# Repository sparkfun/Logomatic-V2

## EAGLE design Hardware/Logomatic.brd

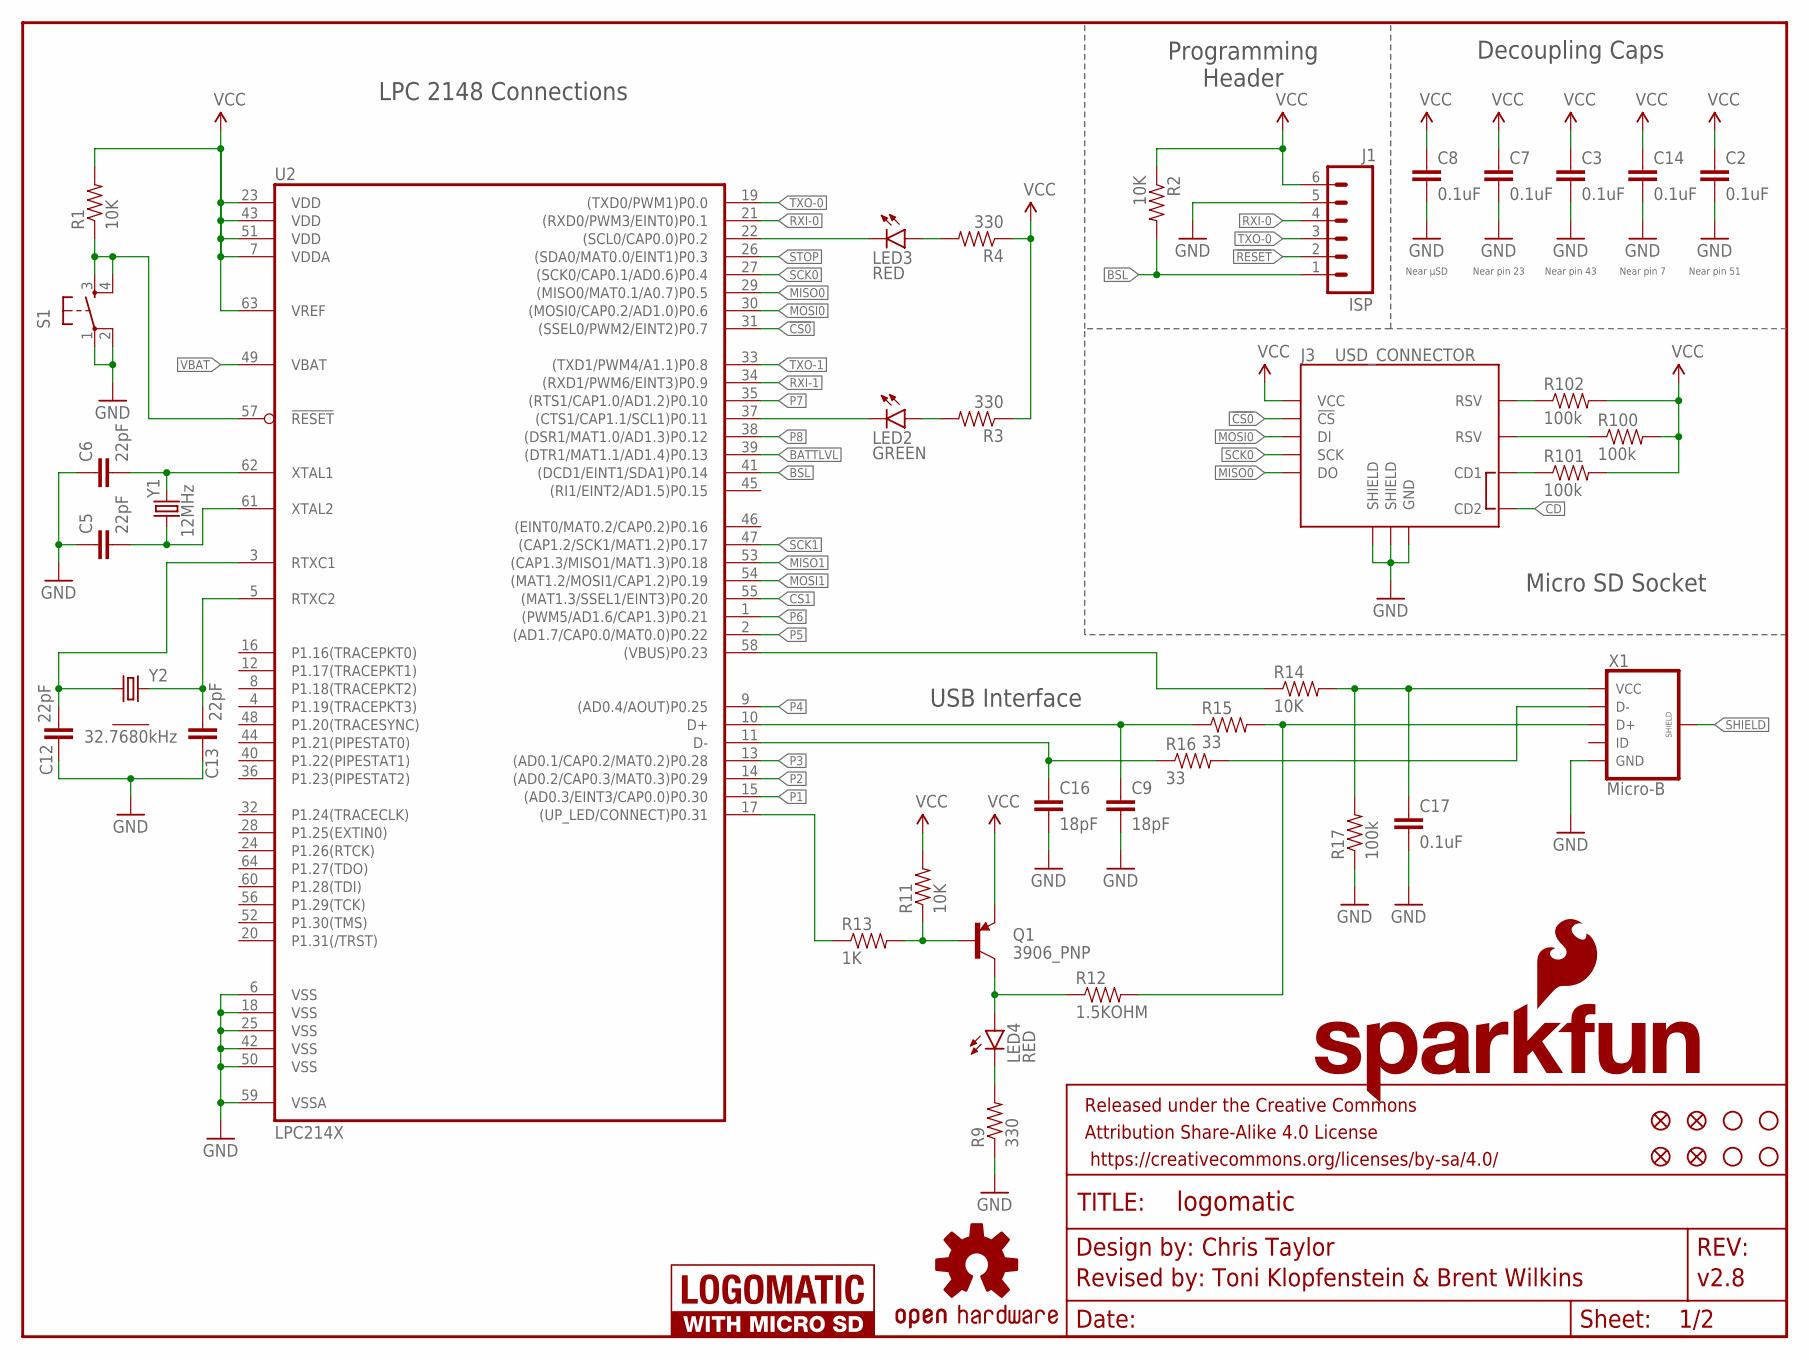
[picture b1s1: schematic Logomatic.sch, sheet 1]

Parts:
C2, C3, C7, C8, C14, C17: 0.1uF; 0603-CAP
C5, C6, C12, C13: 22pF; 0603-CAP
C9, C16: 18pF; 0603-CAP
FD1, FD2, FD100, FD101: FIDUCIAL1X2; FIDUCIAL-1X2
FRAME1: FRAME-LETTER; CREATIVE_COMMONS
H1, H2, H3, H4: STAND-OFF
J1: ISP; 1X06
J3: USD_CONNECTOR; MICRO-SD-SOCKET-PP
LED2: GREEN; LED-0603
LED3, LED4: RED; LED-0603
LOGO1: SFE_LOGO_NAME.1_INCH; SFE_LOGO_NAME_.1
LOGO2: SFE_LOGO_FLAME.1_INCH; SFE_LOGO_FLAME_.1
LOGO100: OSHW-LOGOL; OSHW-LOGO-L
LOGO101: LOGOMATIC_LOGO
Q1: 3906_PNP; SOT23-3
R1, R2, R11, R14: 10K; 0603-RES
R3, R4, R9: 330; 0603-RES
R12: 1.5KOHM; 0603
R13: 1K; 0603-RES
R15, R16: 33; 0603-RES
R17, R100, R101, R102: 100k; 0603-RES
S1: RESET; TACTILE-SWITCH-SMD
U2: LPC214X; LQFP-10X10-64
X1: Micro-B; USB-B-MICRO-SMD_V03
Y1: 12MHz; CRYSTAL-SMD-5X3
Y2: 32.7680kHz; 4-SOJ_5.5MM

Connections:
!CS0: J3.CS (!CS), U2.31 ((SSEL0/PWM2/EINT2)P0.7)
!RESET: J1.2, R1.1, S1.3, S1.4, U2.57 (!RESET)
BATTLVL: U2.39 ((DTR1/MAT1.1/AD1.4)P0.13); also elsewhere on the board
BSL: J1.1, R2.2, U2.41 ((DCD1/EINT1/SDA1)P0.14)
CD: J3.CD2
CS1: U2.55 ((MAT1.3/SSEL1/EINT3)P0.20); also elsewhere on the board
GND: C2.2, C3.2, C5.1, C6.1, C7.2, C8.2, C9.2, C12.1, C13.1, C14.2, C16.2, C17.2, J1.5, J3.GND, J3.GND1 (SHIELD), J3.GND3 (SHIELD), R9.1, R17.1, S1.1, S1.2, U2.6 (VSS), U2.18 (VSS), U2.25 (VSS), U2.42 (VSS), U2.50 (VSS), U2.59 (VSSA), X1.GND; also elsewhere on the board
MISO0: J3.DO, U2.29 ((MISO0/MAT0.1/A0.7)P0.5)
MISO1: U2.53 ((CAP1.3/MISO1/MAT1.3)P0.18); also elsewhere on the board
MOSI0: J3.DI, U2.30 ((MOSI0/CAP0.2/AD1.0)P0.6)
MOSI1: U2.54 ((MAT1.2/MOSI1/CAP1.2)P0.19); also elsewhere on the board
unnamed: J3.CD1, R101.1
unnamed: J3.RSV1 (RSV), R102.1
unnamed: LED3.A, R4.2
unnamed: J3.RSV2 (RSV), R100.1
unnamed: Q1.1 (B), R11.1, R13.2
unnamed: LED2.A, R3.2
unnamed: LED4.C, R9.2
P1: U2.15 ((AD0.3/EINT3/CAP0.0)P0.30); also elsewhere on the board
P2: U2.14 ((AD0.2/CAP0.3/MAT0.3)P0.29); also elsewhere on the board
P3: U2.13 ((AD0.1/CAP0.2/MAT0.2)P0.28); also elsewhere on the board
P4: U2.9 ((AD0.4/AOUT)P0.25); also elsewhere on the board
P5: U2.2 ((AD1.7/CAP0.0/MAT0.0)P0.22); also elsewhere on the board
P6: U2.1 ((PWM5/AD1.6/CAP1.3)P0.21); also elsewhere on the board
P7: U2.35 ((RTS1/CAP1.0/AD1.2)P0.10); also elsewhere on the board
P8: U2.38 ((DSR1/MAT1.0/AD1.3)P0.12); also elsewhere on the board
P-D+: C9.1, R15.1, U2.10 (D+)
P-D-: C16.1, R16.1, U2.11 (D-)
RTXC1: C12.2, U2.3 (RTXC1), Y2.1
RTXC2: C13.2, U2.5 (RTXC2), Y2.4
RXI-0: J1.4, U2.21 ((RXD0/PWM3/EINT0)P0.1)
RXI-1: U2.34 ((RXD1/PWM6/EINT3)P0.9); also elsewhere on the board
SCK0: J3.SCLK (SCK), U2.27 ((SCK0/CAP0.1/AD0.6)P0.4)
SCK1: U2.47 ((CAP1.2/SCK1/MAT1.2)P0.17); also elsewhere on the board
SHIELD: X1.SHIELD1 (SHIELD), X1.SHIELD2 (SHIELD), X1.SHIELD3 (SHIELD)
STAT: LED4.A, Q1.3 (C), R12.1
STAT0: LED3.C, U2.22 ((SCL0/CAP0.0)P0.2)
STAT1: LED2.C, U2.37 ((CTS1/CAP1.1/SCL1)P0.11)
STOP: U2.26 ((SDA0/MAT0.0/EINT1)P0.3); also elsewhere on the board
TXO-0: J1.3, U2.19 ((TXD0/PWM1)P0.0)
TXO-1: U2.33 ((TXD1/PWM4/A1.1)P0.8); also elsewhere on the board
UP_LED: R13.1, U2.17 ((UP_LED/CONNECT)P0.31)
USB_D+: R12.2, R15.2, X1.D+
USB_D-: R16.2, X1.D-
USB_VIN: C17.1, R14.2, R17.2, X1.VBUS (VCC); also elsewhere on the board
VBAT: U2.49 (VBAT); also elsewhere on the board
VBUS: R14.1, U2.58 ((VBUS)P0.23)
VCC: C2.1, C3.1, C7.1, C8.1, C14.1, J1.6, J3.VCC, Q1.2 (E), R1.2, R2.1, R3.1, R4.1, R11.2, R100.2, R101.2, R102.2, U2.7 (VDDA), U2.23 (VDD), U2.43 (VDD), U2.51 (VDD), U2.63 (VREF); also elsewhere on the board
XTAL1: C6.2, U2.62 (XTAL1), Y1.3 (2)
XTAL2: C5.2, U2.61 (XTAL2), Y1.1

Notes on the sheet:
Near pin 23
Near pin 43
Near pin 51
Decoupling Caps
Programming Header
USB Interface
Micro SD Socket
Near pin 7
LPC 2148 Connections
Near µSD

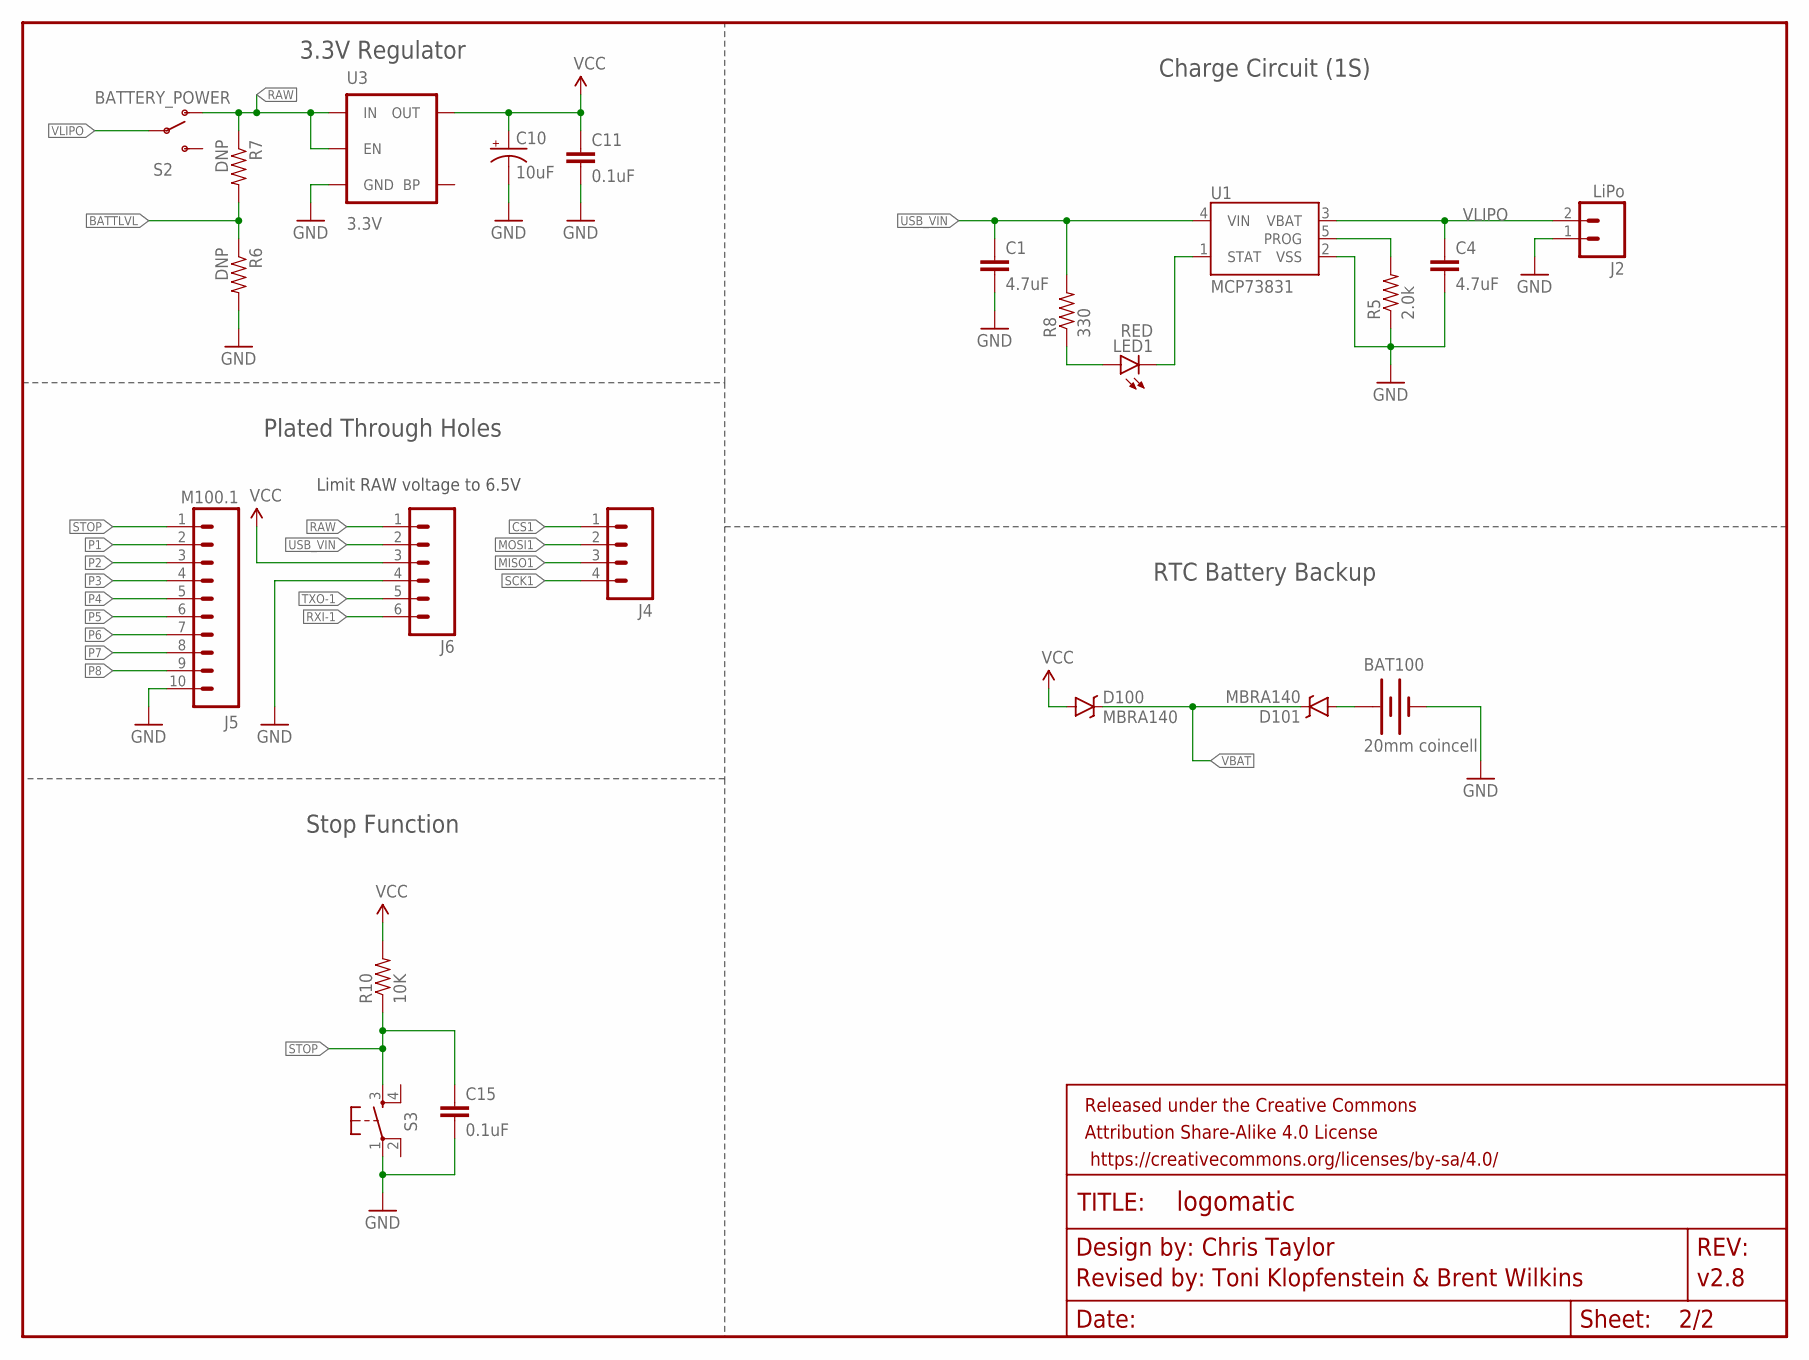
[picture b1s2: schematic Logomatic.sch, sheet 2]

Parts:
BAT100: 20mm coincell; BATTCON_20MM_4LEGS
C1, C4: 4.7uF; 0603-CAP
C10: 10uF; EIA3216
C11, C15: 0.1uF; 0603-CAP
D100, D101: MBRA140; SMA-DIODE
FRAME2: FRAME-LETTERNO_PACKAGE; DUMMY
J2: LiPo; JST-2-SMD
J4: M04PTH; 1X04
J5: M100.1; 1X10
J6: M06SILK_FEMALE_PTH; 1X06
LED1: RED; LED-0603
R5: 2.0k; 0603-RES
R6, R7: DNP; 0603-RES
R8: 330; 0603-RES
R10: 10K; 0603-RES
S2: BATTERY_POWER; AYZ0202
S3: TAC_SWITCHSMD; TACTILE-SWITCH-SMD
U1: MCP73831; SOT23-5
U3: 3.3V; SOT23-5

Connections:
BATTLVL: R6.1, R7.2; also elsewhere on the board
CS1: J4.1; also elsewhere on the board
GND: BAT100.NEGATIVE (-), C1.2, C4.2, C10.C (-), C11.2, C15.2, J2.1 (2), J5.10, J6.4, R5.1, R6.2, S3.1, U1.2 (VSS), U3.2 (GND); also elsewhere on the board
MISO1: J4.3; also elsewhere on the board
MOSI1: J4.2; also elsewhere on the board
unnamed: R5.2, U1.5 (PROG)
unnamed: BAT100.POSITIVE@1 (+), BAT100.POSITIVE@2 (+), BAT100.POSITIVE@3 (+), BAT100.POSITIVE@4 (+), D101.A
unnamed: LED1.C, U1.1 (STAT)
unnamed: LED1.A, R8.1
P1: J5.2; also elsewhere on the board
P2: J5.3; also elsewhere on the board
P3: J5.4; also elsewhere on the board
P4: J5.5; also elsewhere on the board
P5: J5.6; also elsewhere on the board
P6: J5.7; also elsewhere on the board
P7: J5.8; also elsewhere on the board
P8: J5.9; also elsewhere on the board
RAW: J6.1, R7.1, S2.1 (O), U3.1 (IN), U3.3 (EN)
RXI-1: J6.6; also elsewhere on the board
SCK1: J4.4; also elsewhere on the board
STOP: C15.1, J5.1, R10.1, S3.3; also elsewhere on the board
TXO-1: J6.5; also elsewhere on the board
USB_VIN: C1.1, J6.2, R8.2, U1.4 (VIN); also elsewhere on the board
VBAT: D100.C, D101.C; also elsewhere on the board
VCC: C10.A (+), C11.1, D100.A, J6.3, R10.2, U3.5 (OUT); also elsewhere on the board
VLIPO: C4.1, J2.2 (1), S2.2, U1.3 (VBAT)

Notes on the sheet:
3.3V Regulator
Charge Circuit (1S)
Plated Through Holes
Stop Function
RTC Battery Backup
Limit RAW voltage to 6.5V

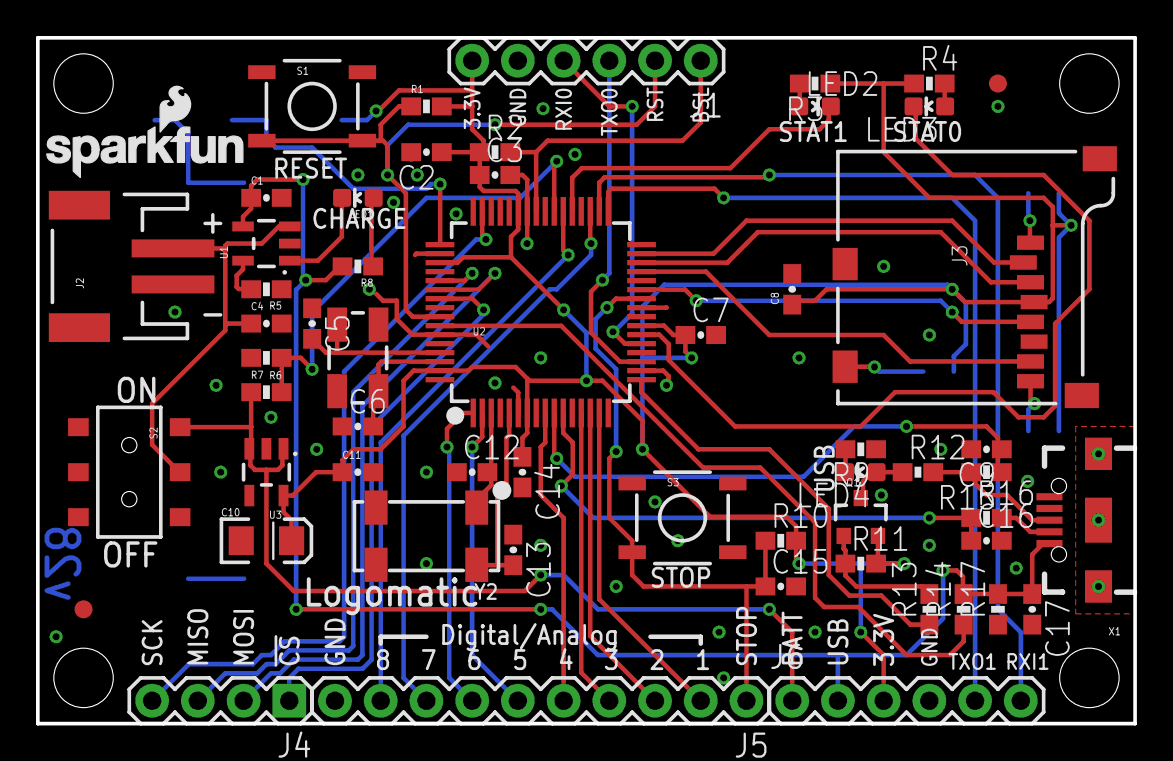
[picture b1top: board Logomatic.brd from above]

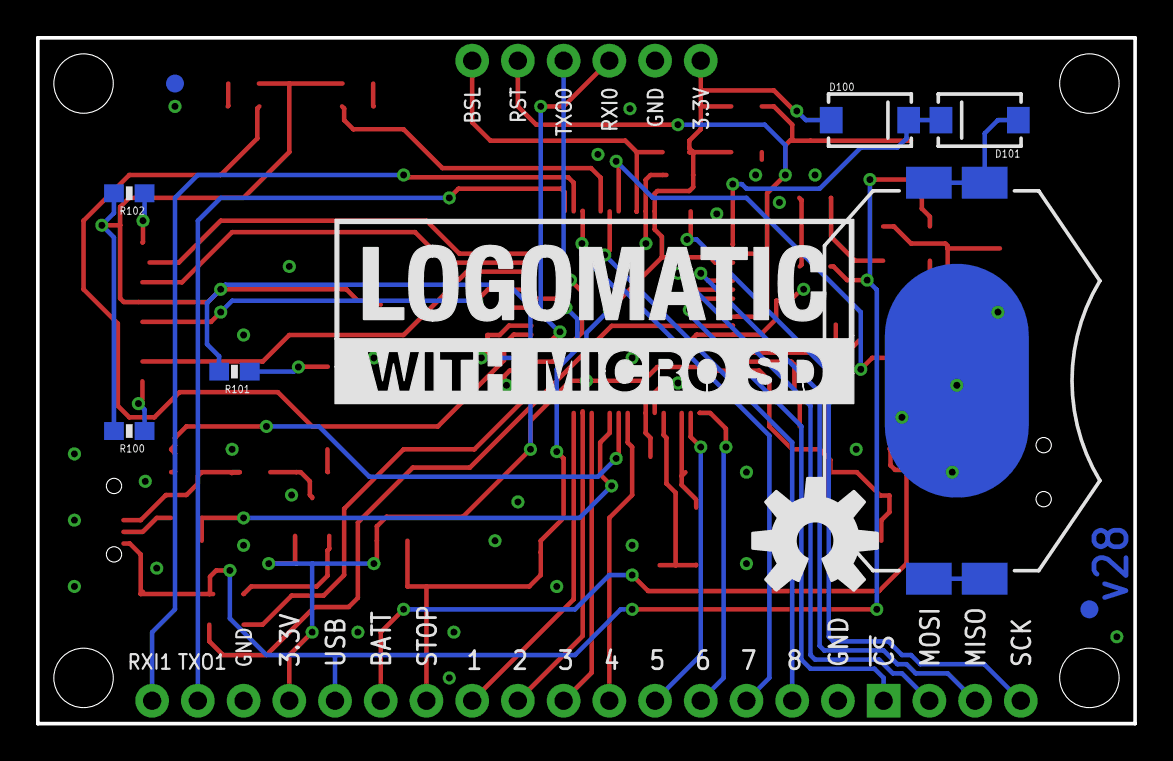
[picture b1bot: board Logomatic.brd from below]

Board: 2 copper layers, 61.0 x 38.1 mm, 74 parts (10 on the bottom side), 55 nets.

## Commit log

2015-12-10 merged the two ADC polling functions into one
2015-12-31 Added coin cell holder
2016-01-06 Tweaks
2016-01-06 Fixed issue #9 on GitHub

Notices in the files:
parts and their libraries:
SparkFun-Aesthetics: Licensing: Creative Commons ShareAlike 4.0 International - https://creativecommons.org/licenses/by-sa/4.0
SparkFun-Aesthetics: Released under the Creative Commons Attribution Share-Alike 4.0 License
SparkFun-Aesthetics: https://creativecommons.org/licenses/by-sa/4.0
